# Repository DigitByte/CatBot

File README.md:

# CatBot

ROS-based quadruped robotics platform for simulation, controls, teleoperation, and learning-by-building.

## Overview

CatBot is a robotics workspace built around a quadruped platform and the software needed to study how that platform moves, senses, and is controlled. The repository combines ROS packages, simulation environments, calibration utilities, and course materials so the project can be used both as a development platform and as a structured learning environment.

The software stack is the primary focus of this repository. Hardware kits, replacement CAD assets, and trademark guidance are tracked separately where noted below.

## What This Repository Includes

- Core gait and control packages for CatBot bring-up and teleoperation.
- Simulation environments in both PyBullet and Gazebo.
- Robot description, calibration, and visualization tooling.
- Navigation, lidar, and vision packages for perception experiments.
- Notebooks, handouts, and course documents for guided learning.

## Key Documents

- [setup.md](./setup.md): environment setup, build steps, simulation bring-up, and hardware notes.
- [COURSE.md](./COURSE.md): 12-week learning path built around CatBot.
- [SYLLABUS.md](./SYLLABUS.md): course description, learning outcomes, and weekly schedule.
- [INSTRUCTOR_GUIDE.md](./INSTRUCTOR_GUIDE.md): teaching notes, lab rubrics, and grading guidance.
- [components.md](./components.md): hardware bill-of-materials reference and sourcing context.
- [HARDWARE.md](./HARDWARE.md): hardware availability status.
- [CONTROLLER_CHEATSHEET.md](./CONTROLLER_CHEATSHEET.md): quick reference for PS5 DualSense control.

## Quick Start

1. Create the development environment with `conda env create -f ros_tf.yml`.
2. Place the repository inside your catkin workspace `src` directory.
3. Build the workspace with `catkin_make`.
4. Launch the simulation with `roslaunch gait_control gait_control_test.launch`.
5. Change gait profiles from a second terminal with `rosservice call /catbot/set_gait "gait_filename: 'diagonal_fast'"`.

## Platform Coverage

| Area | Packages / Docs |
| --- | --- |
| Control | `gait_control`, `catbot_msgs`, `catbot_calibration` |
| Robot model | `catbot_description`, `catbot_visualization` |
| Simulation | `catbot_pybullet`, `catbot_gazebo` |
| Perception | `catbot_lidar`, `catbot_vision`, `catbot_2dnav` |
| Learning material | `notebooks/`, `handouts/`, `COURSE.md`, `SYLLABUS.md` |
| Hardware support | `arduino/`, `electronics/`, `components.md`, `HARDWARE.md` |

## Hardware Note

This repository is intended to remain useful even without a physical robot. The simulation and coursework can be run on a standard ROS workstation, while hardware kits and updated CAD assets are handled separately from the core software repository.

## License

CatBot is released under the terms of the [MIT License](./LICENSE).

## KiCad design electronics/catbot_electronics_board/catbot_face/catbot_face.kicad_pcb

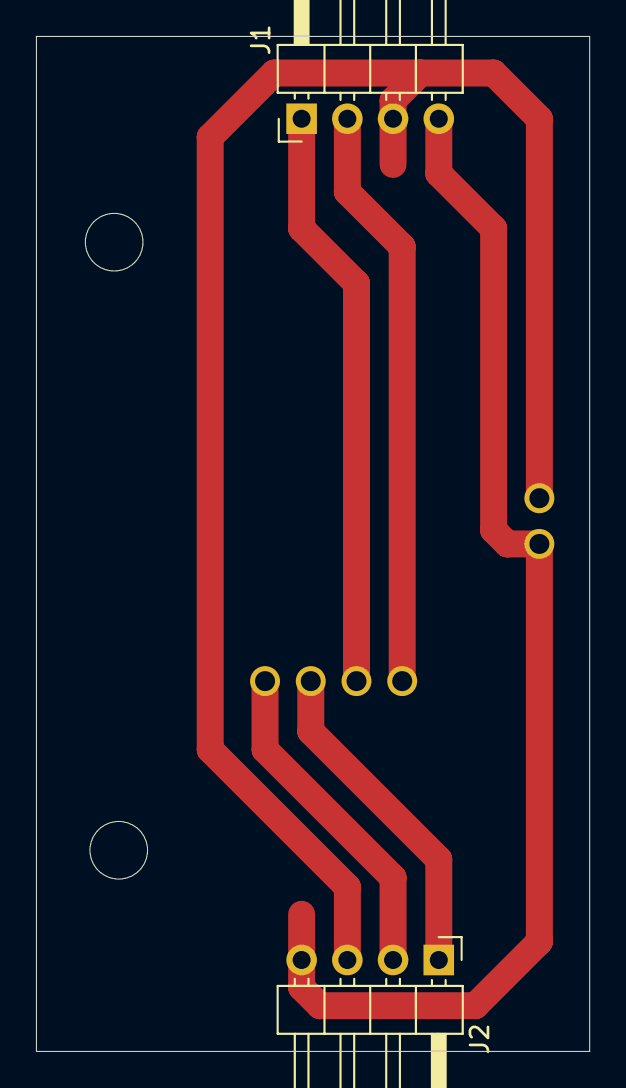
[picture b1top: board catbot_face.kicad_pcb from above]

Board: 2 copper layers, 30.7 x 56.4 mm, 3 parts (1 on the bottom side), 6 nets.

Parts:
IC1: TEENSY_4.0; TEENSY40_cut
J1, J2: eye_left; PinHeader_1x04_P2.54mm_Horizontal

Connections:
+3V3: IC1.16, J1.3, J2.3
GND: IC1.17, J1.4, J2.4
unnamed: IC1.23, J1.2
unnamed: IC1.24, J1.1
unnamed: IC1.25, J2.1
unnamed: IC1.26, J2.2

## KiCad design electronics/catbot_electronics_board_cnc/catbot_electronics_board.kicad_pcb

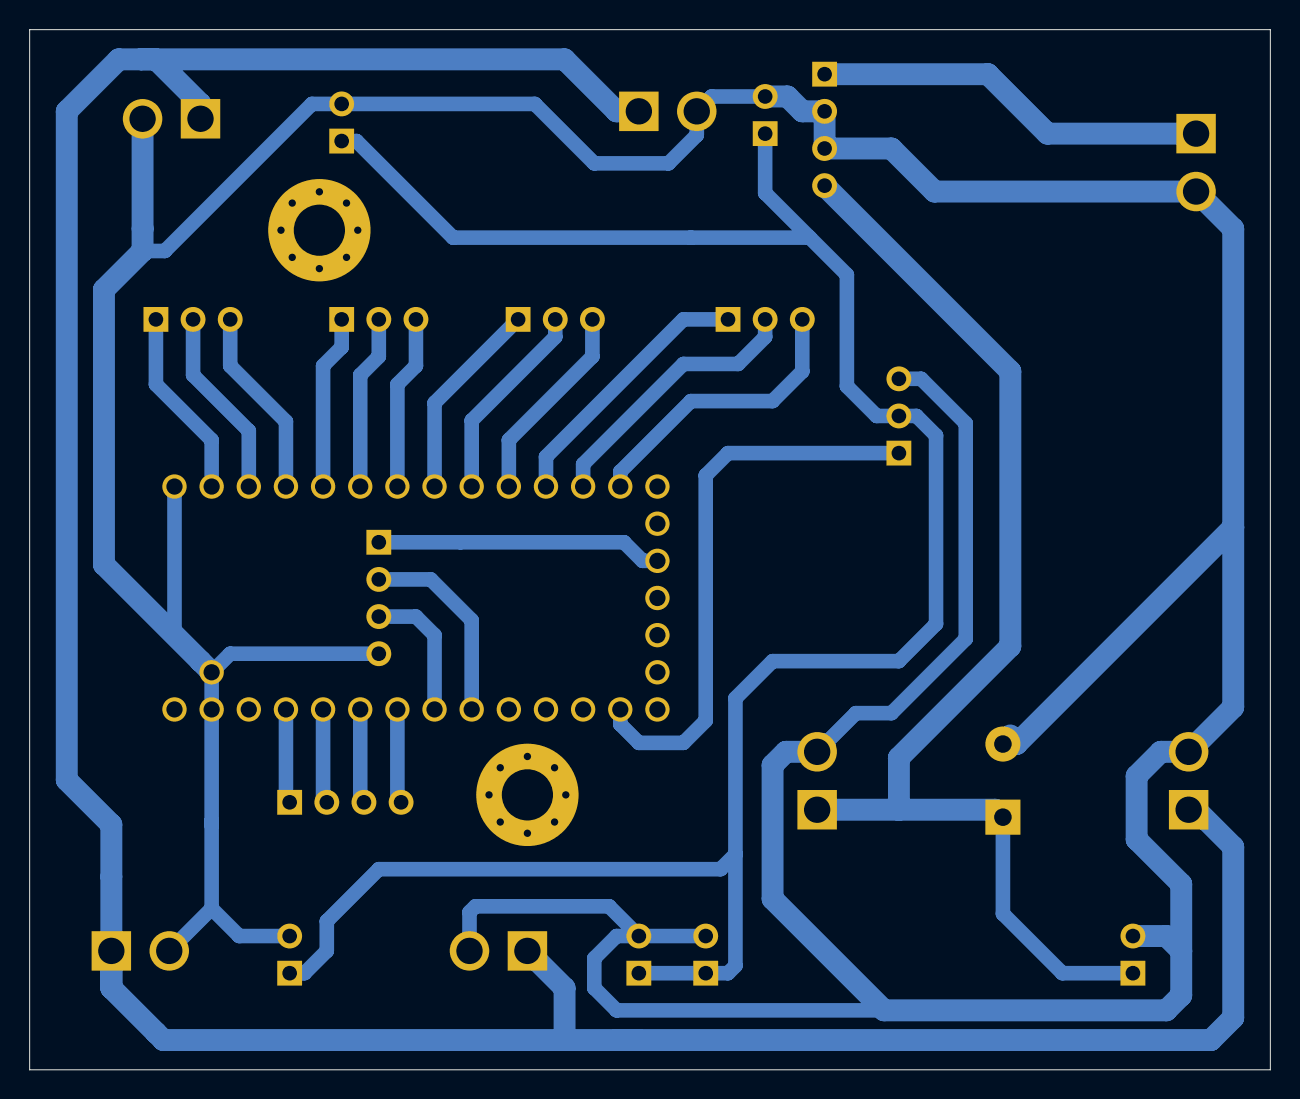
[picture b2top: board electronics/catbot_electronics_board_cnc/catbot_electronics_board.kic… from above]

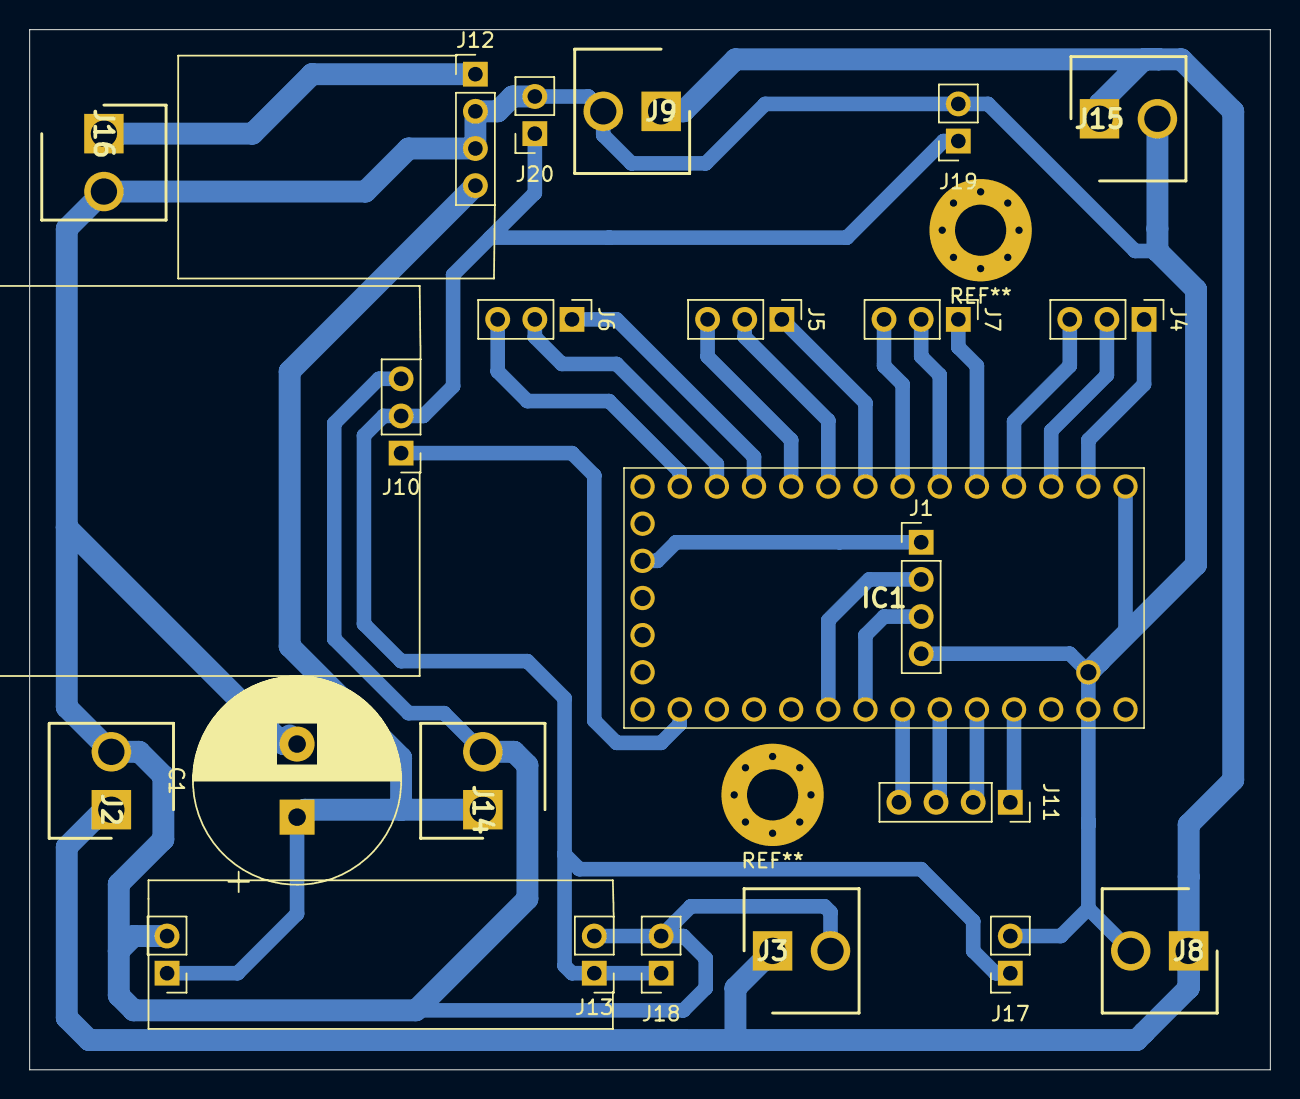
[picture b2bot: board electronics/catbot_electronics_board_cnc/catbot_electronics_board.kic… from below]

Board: 2 copper layers, 84.8 x 71.1 mm, 22 parts (22 on the bottom side), 25 nets.

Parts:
C1: CP; CP_Radial_D14.0mm_P5.00mm
IC1: TEENSY_4.0; TEENSY40
J1: imu_sensor; PinHeader_1x04_P2.54mm_Vertical
J2: power fr; SHDR2W114P0X396_1X2_786X850X940P
J3: power fl; SHDR2W114P0X396_1X2_786X850X940P
J4: leg_fl; PinHeader_1x03_P2.54mm_Vertical
J5: leg_fr; PinHeader_1x03_P2.54mm_Vertical
J6: leg_br; PinHeader_1x03_P2.54mm_Vertical
J7: leg_bl; PinHeader_1x03_P2.54mm_Vertical
J8: power br; SHDR2W114P0X396_1X2_786X850X940P
J9: power bl; SHDR2W114P0X396_1X2_786X850X940P
J10: relay_entry; relay
J11: conn_leg_switch; PinSocket_1x04_P2.54mm_Vertical
J12: 5v_transformer; catbot_5v_transformer
J13: 3.3v transformer; transformer_3.3v
J14: power_battery; SHDR2W114P0X396_1X2_786X850X940P
J15: power servos; SHDR2W114P0X396_1X2_786X850X940P
J16: power_raspi; SHDR2W114P0X396_1X2_786X850X940P
J17: 3.3v_switch_fl; PinSocket_1x02_P2.54mm_Vertical
J18, J19, J20: in_Vcc; PinSocket_1x02_P2.54mm_Vertical

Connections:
+3V3: J10.2, J13.1, J17.1, J18.1, J19.1, J20.1
+5V: J12.1, J16.1
+7.5V: J2.1, J3.1, J8.1, J9.1, J15.1
GND: C1.2, IC1.1, IC1.17, IC1.32, IC1.34, J1.4, J2.2, J3.2, J8.2, J9.2, J10.3, J12.2, J12.3, J13.2, J13.4, J14.2, J15.2, J16.2, J17.2, J18.2, J19.2, J20.2
unnamed: IC1.2, J4.1
unnamed: IC1.3, J4.2
unnamed: IC1.4, J4.3
unnamed: IC1.5, J7.1
unnamed: IC1.6, J7.2
unnamed: IC1.7, J7.3
unnamed: IC1.8, J5.1
unnamed: IC1.9, J5.2
unnamed: IC1.10, J5.3
unnamed: IC1.11, J6.1
unnamed: IC1.12, J6.2
unnamed: IC1.13, J6.3
unnamed: IC1.16, J1.1
unnamed: IC1.21, J10.1
unnamed: IC1.25, J1.2
unnamed: IC1.26, J1.3
unnamed: IC1.27, J11.4
unnamed: IC1.28, J11.3
unnamed: IC1.29, J11.2
unnamed: IC1.30, J11.1
VCC: C1.1, J12.4, J13.3, J14.1

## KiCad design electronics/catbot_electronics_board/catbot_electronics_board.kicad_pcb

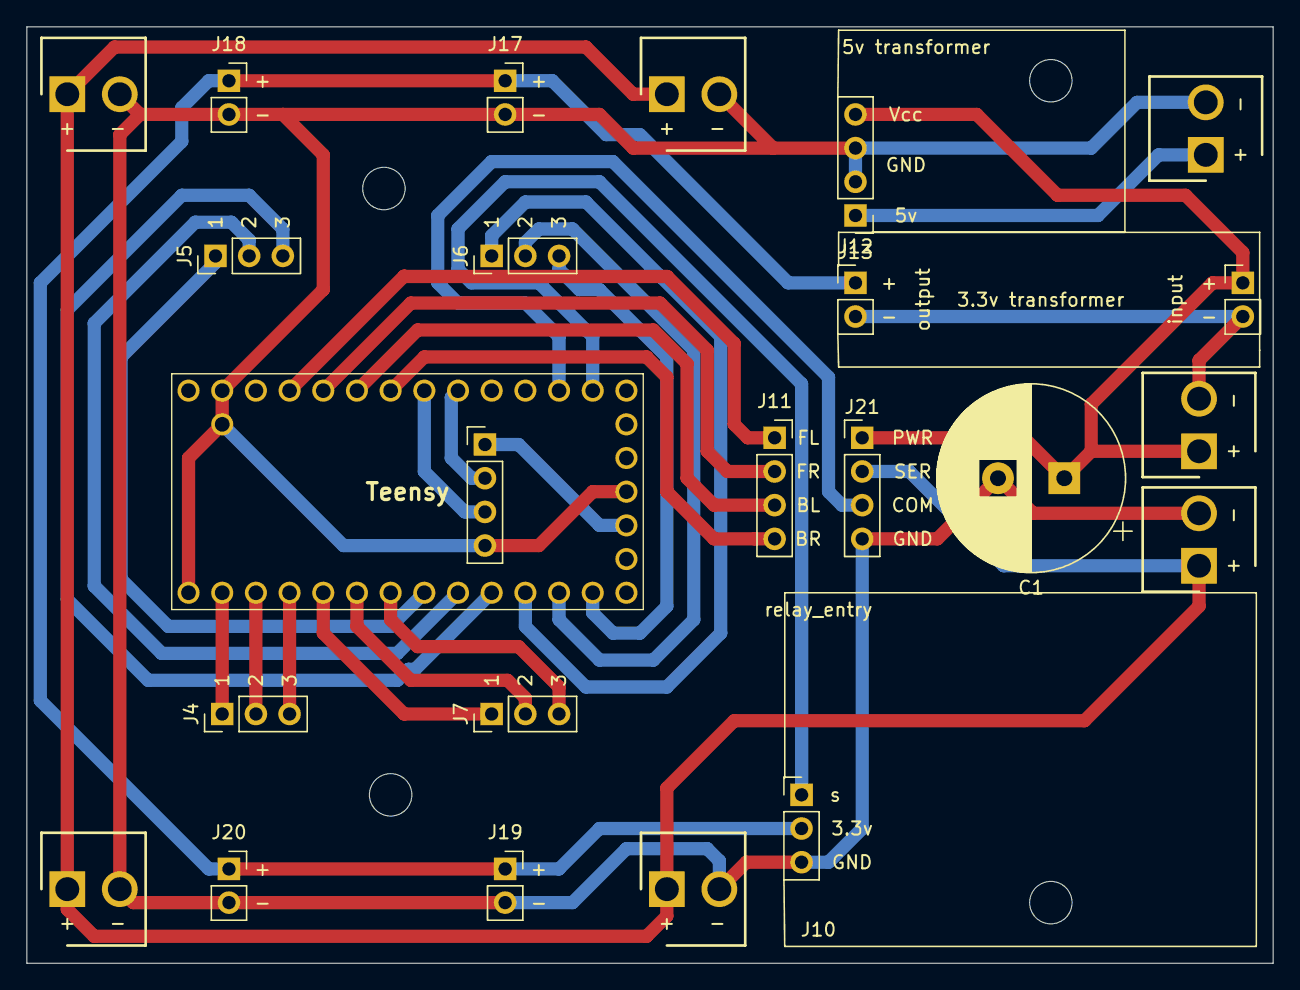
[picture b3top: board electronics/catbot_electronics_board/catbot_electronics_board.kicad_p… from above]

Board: 2 copper layers, 94.0 x 70.6 mm, 23 parts (0 on the bottom side), 26 nets.

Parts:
C1: CP; CP_Radial_D14.0mm_P5.00mm
J1: imu_sensor; IMU_BNO080
J2: power fr; power_servos_connector
J3: power fl; power_servos_connector
J4: leg_fl; leg_connector
J5: leg_fr; leg_connector
J6: leg_br; leg_connector
J7: leg_bl; leg_connector
J8: power br; power_servos_connector
J9: power bl; power_servos_connector
J10: relay_entry; relay
J11: conn_leg_switch; switch_connector
J12: 5v transformer; catbot_5v_transformer
J13: 3.3v transformer; transformer_3.3v
J14: power_battery; power_servos_connector
J15: power servos; power_servos_connector
J16: power_raspi; power_servos_connector
J17: 3.3v_switch_fl; switch_power
J18, J19, J20: in_Vcc; switch_power
J21: leds_status; LED_STATUS
Teensy: TEENSY_4.0; TEENSY40

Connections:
+3V3: J10.2, J13.1, J17.1, J18.1, J19.1, J20.1
+5V: J12.1, J16.1
+7.5V: J2.1, J3.1, J8.1, J9.1, J15.1, J21.2
GND: C1.2, J1.4, J2.2, J3.2, J8.2, J9.2, J10.3, J12.2, J12.3, J13.2, J13.4, J14.2, J15.2, J16.2, J17.2, J18.2, J19.2, J20.2, J21.4, Teensy.1, Teensy.17, Teensy.32, Teensy.34
unnamed: J4.1, Teensy.2
unnamed: J4.2, Teensy.3
unnamed: J4.3, Teensy.4
unnamed: J7.1, Teensy.5
unnamed: J7.2, Teensy.6
unnamed: J7.3, Teensy.7
unnamed: J5.1, Teensy.8
unnamed: J5.2, Teensy.9
unnamed: J5.3, Teensy.10
unnamed: J6.1, Teensy.11
unnamed: J6.2, Teensy.12
unnamed: J6.3, Teensy.13
unnamed: J1.1, Teensy.16
unnamed: J10.1, Teensy.21
unnamed: J21.3, Teensy.22
unnamed: J1.2, Teensy.25
unnamed: J1.3, Teensy.26
unnamed: J11.4, Teensy.27
unnamed: J11.3, Teensy.28
unnamed: J11.2, Teensy.29
unnamed: J11.1, Teensy.30
VCC: C1.1, J12.4, J13.3, J14.1, J21.1

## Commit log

2026-02-12 CatBot initial public release
2026-04-25 Polish CatBot documentation
2026-06-12 Remove repository layout from README
    Removed repository layout section from README.
